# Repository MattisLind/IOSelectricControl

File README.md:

# IOSelectricControl
This project is to create a modern interface to an old IBM 731 IO Selectric terminal.

Back in the mid seventies my father bought a IO Selectric to use with his homebuilt computer. In order to connect it over serial line he had to build a small box with interface electronics. But he also did massive amounts of modifications to the 731 itself.

Top view. Quite a lot of dirt.

Bottom view show all the modifications. There is even a power supply built into it

Unfortunately the documentation that covered what was done back then was scarce so I decvided to remove the modifications and get it back to a more original state. Instead of the control box full of TTL circuits and relays I decided to build a circuit based on a STM32 microcontroller to be able to have it to talk over USB.

## Links

* [Selectric I/O Reference Manual - Section 1](http://bitsavers.org/pdf/ibm/typewriter/selectric/241-5308_IO_SelectricRefMan.pdf)
* [Field Engineering Maintenance Manual Selectric ® I/O Keyboard Printer](http://bitsavers.org/pdf/ibm/typewriter/selectric/S225-1726-7_IOseleMnt_Nov70.pdf)

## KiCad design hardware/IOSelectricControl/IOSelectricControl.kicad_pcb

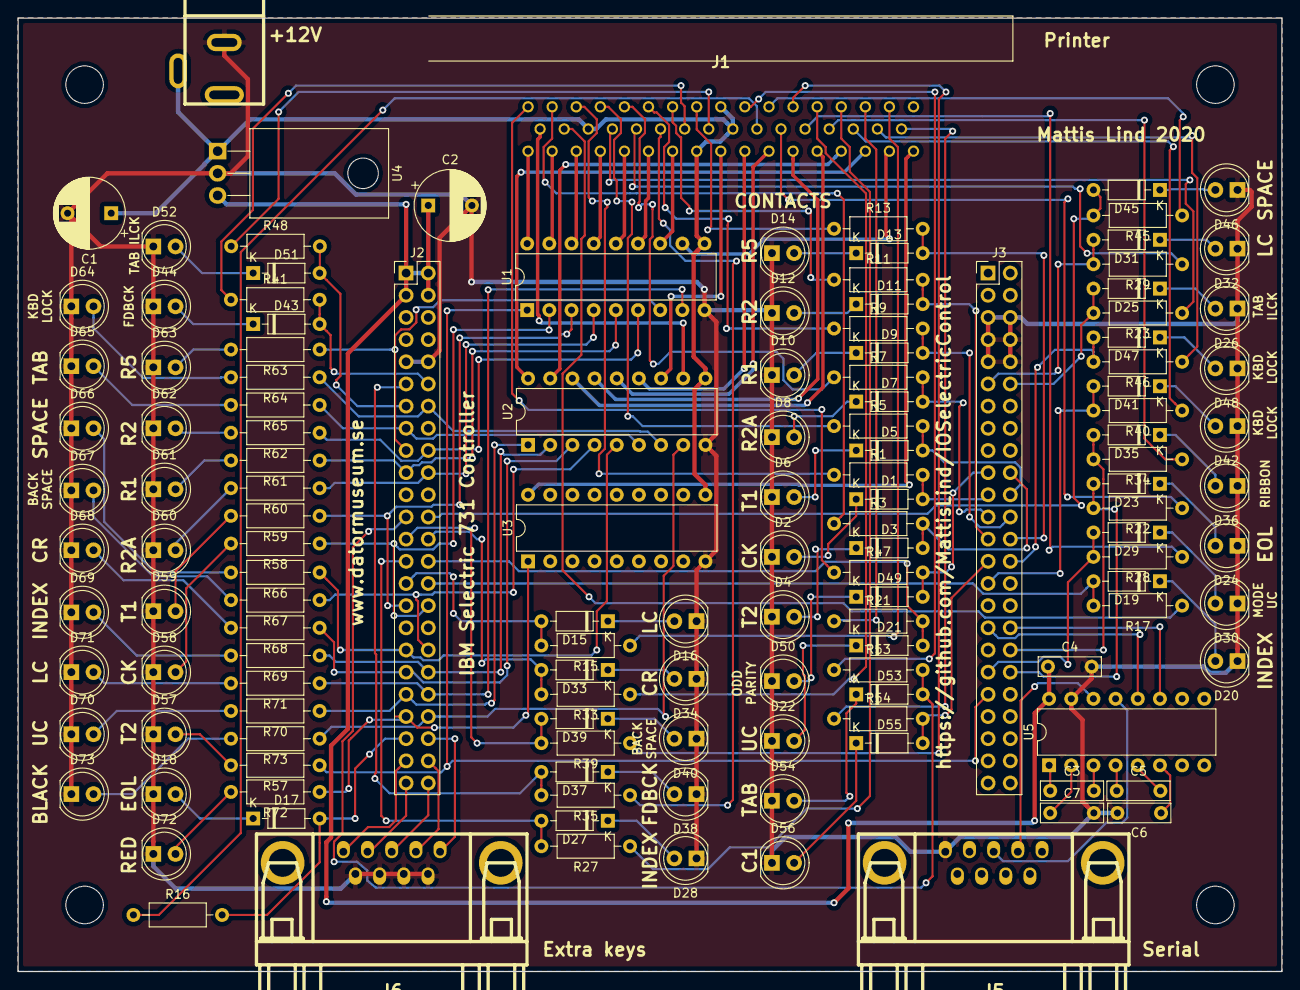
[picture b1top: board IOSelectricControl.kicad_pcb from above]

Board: 2 copper layers, 144.8 x 109.2 mm, 136 parts (0 on the bottom side), 153 nets.

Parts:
C1: 47u; CP_Radial_D8.0mm_P5.00mm
C2: 100u; CP_Radial_D8.0mm_P5.00mm
C3, C4, C5, C6, C7: 0.1u; C_Rect_L7.0mm_W2.0mm_P5.00mm
D1, D3, D5, D7, D9, D11, D13, D15, D17, D19, D21, D23, D25, D27, D29, D31, D33, D35, D37, D39, D41, D43, D45, D47, D49, D51, D53, D55: 1N4148; D_DO-35_SOD27_P7.62mm_Horizontal
D2, D4, D6, D8, D10, D12, D14, D36, D50: YEL; LED_D5.0mm
D16, D22, D28, D34, D40, D46, D54: AMB; LED_D5.0mm
D18, D20, D26, D32, D44, D48: RED; LED_D5.0mm
D24, D30, D38, D42, D52, D56: GRN; LED_D5.0mm
D57, D58, D59, D60, D61, D62, D63: BLU; LED_D5.0mm
D64, D65, D66, D67, D68, D69, D70, D71, D72, D73: ORA; LED_D5.0mm
J1: DB-50; DD50S564TLF
J2, J3: HEADER_24x2; PinHeader_2x24_P2.54mm_Vertical
J4: +12V; dc_socket
J5: Serial; DB_9F
J6: Extra keys; DB_9F
R1, R3, R5, R7, R9, R11, R13, R15, R16, R17, R21, R22, R23, R27, R28, R29, R33, R34, R35, R39, R40, R41, R45, R46, R47, R48, R53, R54: 4,7k; R_Axial_DIN0207_L6.3mm_D2.5mm_P10.16mm_Horizontal
R57, R58, R59, R60, R61, R62, R63, R64, R65, R66, R67, R68, R69, R70, R71, R72, R73: 470; R_Axial_DIN0207_L6.3mm_D2.5mm_P10.16mm_Horizontal
U1, U2, U3: ULN2803A; DIP-18_W7.62mm
U4: L7805; TO-220-3_Horizontal_TabDown
U5: MAX202; DIP-16_W7.62mm

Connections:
+5V: C2.1, C4.1, J2.1, J2.2, J2.3, J2.4, U4.3, U5.16
+12V: C1.1, J1.8, J1.20, J1.26, J1.42, J4.1, U1.10, U2.10, U3.10, U4.1
/A: J1.1, U1.18
/AA: J1.44, R45.1
/B: J1.2, U1.17
/BB: J1.45, R39.1
/BREAK: J2.44, J6.1
/C: J1.3, U1.16
/CC: J1.46, R33.1
/CON_C1_NC: J1.19, R17.1
/CON_C1_NO: J1.33, R54.1
/CON_CK_NO: J1.36, R1.1
/CON_EOL_NC: J1.27, R16.1
/CON_EOL_NO: J1.28, R22.1
/CON_FDBCK_NC: J1.23, R35.1
/CON_FDBCK_NO: J1.24, R41.1
/CON_INDEX_NO: J1.47, R27.1
/CON_KBD_NC: J1.31, R40.1
/CON_KBD_NO: J1.32, R46.1
/CON_LC_NO: J1.49, R15.1
/CON_MODE_LC_NC: J1.22, R29.1
/CON_MODE_UC_NO: J1.29, R28.1
/CON_ODD_PARITY: J1.34, R47.1
/CON_R1_NO: J1.39, R9.1
/CON_R2A_NO: J1.38, R7.1
/CON_R2_NO: J1.40, R11.1
/CON_R5_NO: J1.41, R13.1
/CON_RIBBON_NO: J1.30, R34.1
/CON_T1_NO: J1.37, R5.1
/CON_T2_NO: J1.35, R3.1
/CON_TAB_ILCK_NC: J1.21, R23.1
/CON_TAB_ILCK_NO: J1.25, R48.1
/CON_TAB_NO: J1.43, R53.1
/CON_UC_NO: J1.48, R21.1
/CTRL: J2.46, J6.2
/D: J1.4, U1.15
/E: J1.5, U1.14
/EIA_RX: J5.3, U5.13
/EIA_TX: J5.2, U5.14
/F: J1.6, U1.13
/H: J1.7, U1.12
/K: J1.9, U2.12
/L: J1.10, U2.13
/M: J1.11, U2.14
/N: J1.12, U2.15
/P: J1.13, U2.16
/PAR0: J2.47, J6.4
/PAR1: J2.48, J6.3
/PARODD: J2.45, J6.5
/R: J1.14, U2.17
/S: J1.15, U2.18
/SER_RX: J3.33, U5.12
/SER_TX: J3.34, U5.11
/SOL_BLACK: J1.18, U2.11
/SOL_LC: J1.16, U1.11
/SOL_RED: J1.17, U3.18
/STM_BLACK: J2.42, R73.1, U2.8
/STM_BSP: J2.36, R67.1, U2.4
/STM_BSP_NO: D39.2, J2.25, R39.2
/STM_C1_NC: D19.2, J2.30, R17.2
/STM_C1_NO: D55.2, J3.27, R54.2
/STM_CK: J2.32, R58.1, U1.2
/STM_CK_NO: D1.2, J3.21, R1.2
/STM_CR: J2.37, R68.1, U2.3
/STM_CR_NO: D33.2, J2.26, R33.2
/STM_EOL_NC: D17.2, J2.43, R16.2
/STM_EOL_NO: D23.2, J3.38, R22.2
/STM_FDBCK_NC: D37.2, J2.11, R35.2
/STM_FDBCK_NO: D43.2, J2.12, R41.2
/STM_INDEX: J2.38, R69.1, U2.2
/STM_INDEX_NO: D27.2, J2.27, R27.2
/STM_KBD_LOCK: J2.14, R64.1, U2.7
/STM_KBD_NC: D41.2, J3.29, R40.2
/STM_KBD_NO: D47.2, J3.28, R46.2
/STM_LC: J2.40, R71.1, U1.8
/STM_LC_NO: D15.2, J2.29, R15.2
/STM_MODE_LC_NC: D31.2, J3.11, R29.2
/STM_MODE_UC_NO: D29.2, J3.37, R28.2
/STM_ODD_PAR_NO: D49.2, J3.19, R47.2
/STM_R1: J2.19, R61.1, U1.5
/STM_R1_NO: D9.2, J3.24, R9.2
/STM_R2: J2.18, R62.1, U1.6
/STM_R2A: J2.20, R60.1, U1.4
/STM_R2A_NO: D7.2, J3.23, R7.2
/STM_R2_NO: D11.2, J3.25, R11.2
/STM_R5: J2.17, R63.1, U1.7
/STM_R5_NO: D13.2, J3.26, R13.2
/STM_RED: J2.41, R72.1, U3.1
/STM_RIBBON_NO: D35.2, J3.36, R34.2
/STM_SP: J2.35, R66.1, U2.5
/STM_SP_NO: D45.2, J2.24, R45.2
/STM_T1: J2.31, R59.1, U1.3
/STM_T1_NO: D5.2, J3.22, R5.2
/STM_T2: J3.39, R57.1, U1.1
/STM_T2_NO: D3.2, J3.20, R3.2
/STM_TAB: J2.15, R65.1, U2.6
/STM_TAB_ILCK_NC: D25.2, J3.12, R23.2
/STM_TAB_ILCK_NO: D51.2, J2.13, R48.2
/STM_TAB_NO: D53.2, J2.23, R53.2
/STM_UC: J2.39, R70.1, U2.1
/STM_UC_NO: D21.2, J2.28, R21.2
GND: C1.2, C2.2, C4.2, C6.2, C7.2, D2.1, D4.1, D6.1, D8.1, D10.1, D12.1, D14.1, D16.1, D18.1, D20.1, D22.1, D24.1, D26.1, D28.1, D30.1, D32.1, D34.1, D36.1, D38.1, D40.1, D42.1, D44.1, D46.1, D48.1, D50.1, D52.1, D54.1, D56.1, D57.1, D58.1, D59.1, D60.1, D61.1, D62.1, D63.1, D64.1, D65.1, D66.1, D67.1, D68.1, D69.1, D70.1, D71.1, D72.1, D73.1, J2.9, J2.10, J3.5, J3.6, J3.7, J3.8, J3.9, J3.10, J4.2, J5.5, J6.6, J6.7, J6.8, J6.9, U1.9, U2.9, U3.9, U4.2, U5.15
unnamed: C3.1, U5.1
unnamed: C3.2, U5.3
unnamed: C5.1, U5.4
unnamed: C5.2, U5.5
unnamed: C6.1, U5.6
unnamed: C7.1, U5.2
unnamed: D1.1, D2.2
unnamed: D3.1, D4.2
unnamed: D5.1, D6.2
unnamed: D7.1, D8.2
unnamed: D9.1, D10.2
unnamed: D11.1, D12.2
unnamed: D13.1, D14.2
unnamed: D15.1, D16.2
unnamed: D17.1, D18.2
unnamed: D19.1, D20.2
unnamed: D21.1, D22.2
unnamed: D23.1, D24.2
unnamed: D25.1, D26.2
unnamed: D27.1, D28.2
unnamed: D29.1, D30.2
unnamed: D31.1, D32.2
unnamed: D33.1, D34.2
unnamed: D35.1, D36.2
unnamed: D37.1, D38.2
unnamed: D39.1, D40.2
unnamed: D41.1, D42.2
unnamed: D43.1, D44.2
unnamed: D45.1, D46.2
unnamed: D47.1, D48.2
unnamed: D49.1, D50.2
unnamed: D51.1, D52.2
unnamed: D53.1, D54.2
unnamed: D55.1, D56.2
unnamed: D57.2, R57.2
unnamed: D58.2, R58.2
unnamed: D59.2, R59.2
unnamed: D60.2, R60.2
unnamed: D61.2, R61.2
unnamed: D62.2, R62.2
unnamed: D63.2, R63.2
unnamed: D64.2, R64.2
unnamed: D65.2, R65.2
unnamed: D66.2, R66.2
unnamed: D67.2, R67.2
unnamed: D68.2, R68.2
unnamed: D69.2, R69.2
unnamed: D70.2, R70.2
unnamed: D71.2, R71.2
unnamed: D72.2, R72.2
unnamed: D73.2, R73.2

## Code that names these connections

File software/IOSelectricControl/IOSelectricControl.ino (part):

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#define SOL_CR PE9
#define SOL_INDEX PE10
#define SOL_UC PE11
#define SOL_LC PE12
#define SOL_RED PE13
#define SOL_BLACK PE14
#define EOL_NC PE15
#define MODE_LC_NC PE1
#define TAB_ILCK_NC PE0
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  digitalWrite(SOL_UC, LOW);
  pinMode(SOL_UC, OUTPUT);  
  digitalWrite(SOL_LC, LOW);
  pinMode(SOL_LC, OUTPUT);  
  digitalWrite(SOL_RED, LOW);
  pinMode(SOL_RED, OUTPUT); 
  digitalWrite(SOL_BLACK, LOW);
  pinMode(SOL_BLACK, OUTPUT); 
  pinMode(EOL_NC, INPUT_PULLDOWN);
  pinMode(MODE_LC_NC, INPUT_PULLDOWN);
  pinMode(TAB_ILCK_NC, INPUT_PULLDOWN);  
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
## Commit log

2020-10-11 First step to experiment with the IO Selectric.
2020-10-11 Added correspondance code translation table.
2020-10-11 Added links to documents.
2020-10-11 Spelling
2020-10-11 Added methods to energize solenoids
2020-10-11 First attempt to print a line of text.
2020-10-12 Added some pictures of the IO Selectric
2020-10-12 Added a command line tool parser.
2020-10-13 Added printing a line at once.
2020-10-16 Work in progress.
2020-10-17 Fixing 1 and c characters.
2020-12-09 Added Kicad files.
2021-02-07 Last commit before the catastrophic failure of my nice little 731. I might never get back to this project :-(
